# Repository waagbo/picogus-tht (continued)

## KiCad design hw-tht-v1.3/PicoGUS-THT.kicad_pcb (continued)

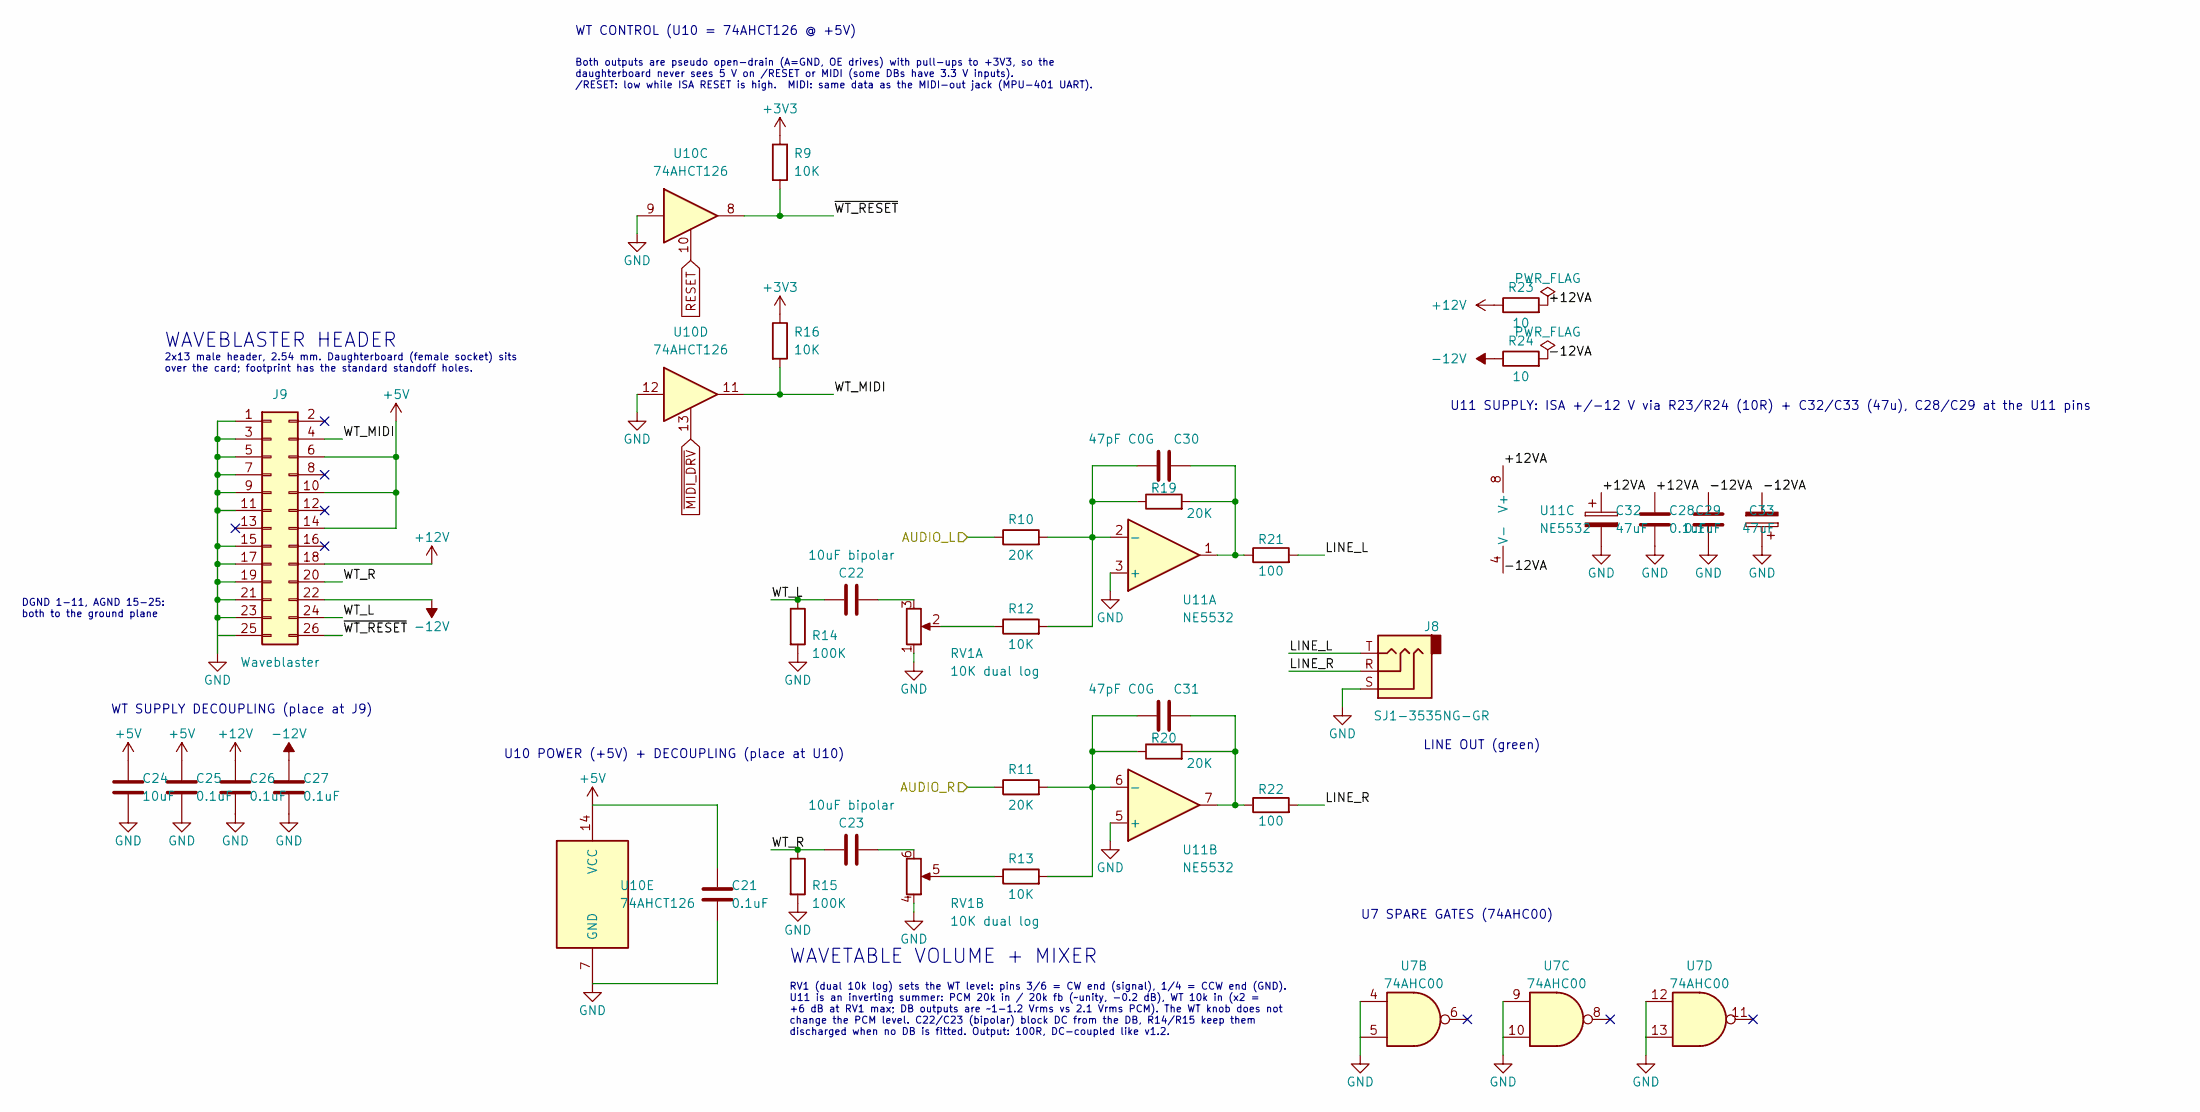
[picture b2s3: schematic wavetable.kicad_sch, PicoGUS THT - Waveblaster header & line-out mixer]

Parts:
C21, C25, C26, C27, C28, C29: 0.1uF; C_Disc_D5.0mm_W2.5mm_P5.00mm; MPN RDER71H104K0M1H03A; DigiKey 490-9144-1-ND
C22, C23: 10uF bipolar; C_Radial_D6.3mm_H11.0mm_P2.50mm; MPN ECE-A1HN100U; DigiKey P1280-ND
C24: 10uF; C_Disc_D5.0mm_W2.5mm_P5.00mm; MPN RCER71H106MWK1H03B; DigiKey 490-11888-ND
C30, C31: 47pF C0G; C_Disc_D5.0mm_W2.5mm_P5.00mm; MPN K470J15C0GF5TH5; DigiKey BC1038CT-ND
C32, C33: 47uF; CP_Radial_D5.0mm_P2.00mm; MPN 35YXJ47M5X11; DigiKey 1189-2919-ND
J8: SJ1-3535NG-GR; Jack_3.5mm_CUI_SJ1-3535NG_Horizontal; MPN SJ1-3535NG-GR; DigiKey CP1-3535NG-GR-ND
J9: Waveblaster; Wavetable_NoMountingHoles; MPN 77313-118-26LF; DigiKey 609-5706-ND
R9, R12, R13, R16: 10K; R_Axial_DIN0207_L6.3mm_D2.5mm_P10.16mm_Horizontal; MPN MFR-25FBF52-10K; DigiKey 10.0KXBK-ND
R10, R11, R19, R20: 20K; R_Axial_DIN0207_L6.3mm_D2.5mm_P10.16mm_Horizontal; MPN MFR-25FBF52-20K; DigiKey 20.0KXBK-ND
R14, R15: 100K; R_Axial_DIN0207_L6.3mm_D2.5mm_P10.16mm_Horizontal; MPN MFR-25FBF52-100K; DigiKey 100KXBK-ND
R21, R22: 100; R_Axial_DIN0207_L6.3mm_D2.5mm_P10.16mm_Horizontal; MPN MFR-25FBF52-100R; DigiKey 100XBK-ND
R23, R24: 10; R_Axial_DIN0207_L6.3mm_D2.5mm_P10.16mm_Horizontal; MPN MFR-25FBF52-10R; DigiKey 10.0XBK-ND
RV1: 10K dual log; Potentiometer_Alps_RK097_Dual_Horizontal_Switch; MPN PTD902-2015F-A103; DigiKey PTD902-2015F-A103-ND
U7: 74AHC00; DIP-14_W7.62mm; MPN SN74AHC00N; DigiKey 296-4510-5-ND
U10: 74AHCT126; DIP-14_W7.62mm; MPN SN74AHCT126N; DigiKey 296-4659-5-ND
U11: NE5532; DIP-8_W7.62mm; MPN NE5532P; DigiKey 296-1410-5-ND

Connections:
+3V3: R9.1, R16.1; also elsewhere on the board
+5V: C21.1, C24.1, C25.1, J9.6, J9.10, J9.14, U10.14 (VCC); also elsewhere on the board
+12V: C26.1, J9.18, R23.1; also elsewhere on the board
-12V: C27.1, J9.22, R24.1; also elsewhere on the board
/PCM5100 audio/AUDIO_L: R10.1; also elsewhere on the board
/PCM5100 audio/AUDIO_R: R11.1; also elsewhere on the board
/Wavetable & line out/+12VA: C28.1, C32.1, R23.2, U11.8 (V+)
/Wavetable & line out/-12VA: C29.2, C33.2, R24.2, U11.4 (V-)
/Wavetable & line out/LINE_L: J8.T, R21.2
/Wavetable & line out/LINE_R: J8.R, R22.2
/Wavetable & line out/WT_L: C22.1, J9.24, R14.1
/Wavetable & line out/WT_MIDI: J9.4, R16.2, U10.11
/Wavetable & line out/WT_R: C23.1, J9.20, R15.1
/Wavetable & line out/~WT_RESET: J9.26, R9.2, U10.8
GND: C21.2, C24.2, C25.2, C26.2, C27.2, C28.2, C29.1, C32.2, C33.1, J8.S, J9.1, J9.3, J9.5, J9.7, J9.9, J9.11, J9.15, J9.17, J9.19, J9.21, J9.23, J9.25, R14.2, R15.2, RV1.1, RV1.4, U7.4, U7.5, U7.9, U7.10, U7.12, U7.13, U10.7 (GND), U10.9, U10.12, U11.3 (+), U11.5 (+); also elsewhere on the board
unnamed: C22.2, RV1.3
unnamed: C23.2, RV1.6
unnamed: C30.2, R19.2, R21.1, U11.1
unnamed: C31.2, R20.2, R22.1, U11.7
unnamed: R12.1, RV1.2
unnamed: R13.1, RV1.5
unnamed: C30.1, R10.2, R12.2, R19.1, U11.2 (-)
unnamed: C31.1, R11.2, R13.2, R20.1, U11.6 (-)
RESET: U10.10; also elsewhere on the board
~MIDI_DRV: U10.13; also elsewhere on the board

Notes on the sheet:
DGND 1-11, AGND 15-25: both to the ground plane
WAVEBLASTER HEADER
2x13 male header, 2.54 mm. Daughterboard (female socket) sits over the card; footprint has the standard standoff holes.
WT SUPPLY DECOUPLING (place at J9)
U10 POWER (+5V) + DECOUPLING (place at U10)
WT CONTROL (U10 = 74AHCT126 @ +5V)
Both outputs are pseudo open-drain (A=GND, OE drives) with pull-ups to +3V3, so the daughterboard never sees 5 V on /RESET or MIDI (some DBs have 3.3 V inputs). /RESET: low while ISA RESET is high. MIDI: same data as the MIDI-out jack (MPU-401 UART).
U11 SUPPLY: ISA +/-12 V via R23/R24 (10R) + C32/C33 (47u), C28/C29 at the U11 pins
WAVETABLE VOLUME + MIXER
RV1 (dual 10k log) sets the WT level: pins 3/6 = CW end (signal), 1/4 = CCW end (GND). U11 is an inverting summer: PCM 20k in / 20k fb (~unity, -0.2 dB), WT 10k in (x2 = +6 dB at RV1 max; DB outputs are ~1-1.2 Vrms vs 2.1 Vrms PCM). The WT knob does not change the PCM level. C22/C23 (bipolar) block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
LINE OUT (green)
U7 SPARE GATES (74AHC00)

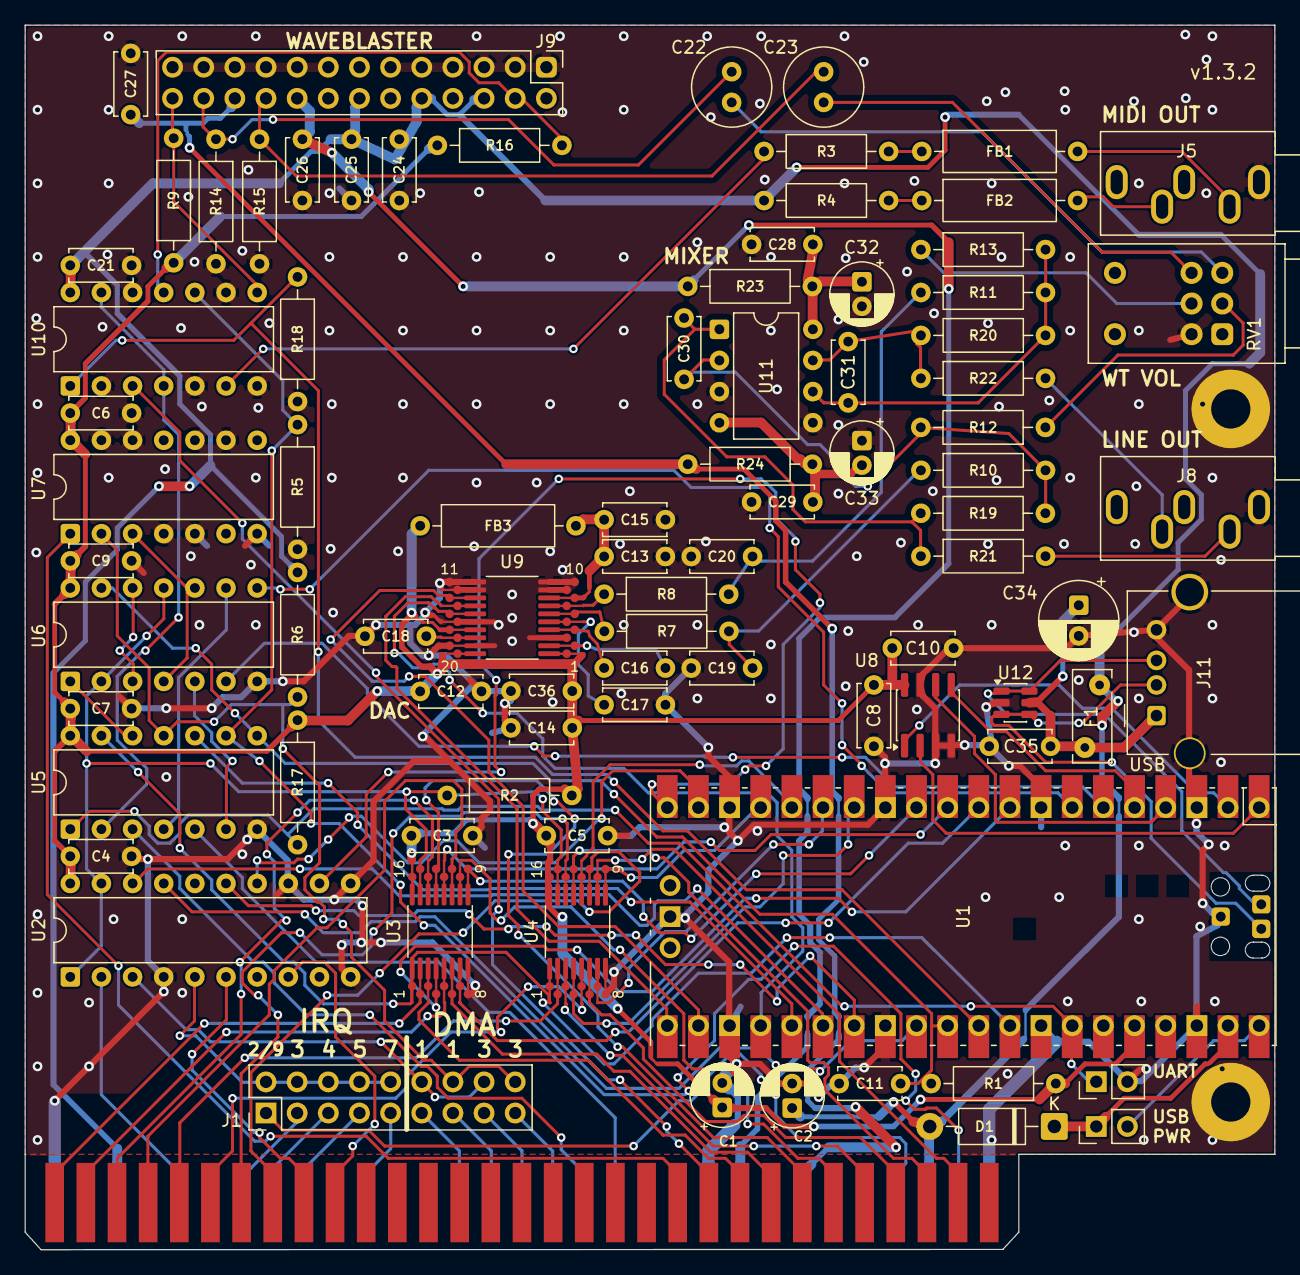
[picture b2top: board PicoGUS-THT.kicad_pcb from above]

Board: 2 copper layers, 101.9 x 99.8 mm, 88 parts (0 on the bottom side), 110 nets.

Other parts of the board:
C34: 220uF; CP_Radial_D6.3mm_P2.50mm
C35: 0.1uF; C_Disc_D5.0mm_W2.5mm_P5.00mm
F1: 0.5A PTC; Fuse_Bourns_MF-RHT050
J11: USB-A; USB_A_Molex_67643_Horizontal
U12: USBLC6-2SC6; SOT-23-6

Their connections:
+5V: F1.1; also elsewhere on the board
/USB host port/VBUS_USB: C34.1, C35.1, F1.2, J11.1, U12.5
GND: C34.2, C35.2, J11.4, J11.SH, U12.2; also elsewhere on the board
USB_DM: J11.2, U12.3, U12.4; also elsewhere on the board
USB_DP: J11.3, U12.1, U12.6; also elsewhere on the board

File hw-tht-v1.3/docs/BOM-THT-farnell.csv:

Quantity,Manufacturer Part Number,Manufacturer,Customer Part Number,Description
1,SC0915,Raspberry Pi,PicoGUS-THT-1.3.2: U1,Raspberry Pi Pico
1,SN74AHC244N,Texas Instruments,PicoGUS-THT-1.3.2: U2,74AHC244
2,SN74CB3T3257PWR,Texas Instruments,"PicoGUS-THT-1.3.2: U3,U4",SN74CB3T3257
1,SN74AHC14N,Texas Instruments,PicoGUS-THT-1.3.2: U5,74AHC14
2,SN74AHC00N,Texas Instruments,"PicoGUS-THT-1.3.2: U6,U7",74AHC00
1,APS6404L-3SQR-SN,AP Memory,PicoGUS-THT-1.3.2: U8,APS6404L-3SQR-SN
1,PCM5100APWR,Texas Instruments,PicoGUS-THT-1.3.2: U9,PCM5100A
1,SN74AHCT126N,Texas Instruments,PicoGUS-THT-1.3.2: U10,74AHCT126
1,1N5819RLG,onsemi,PicoGUS-THT-1.3.2: D1,1N5819
2,RNMF14FTC220R,Stackpole,"PicoGUS-THT-1.3.2: R3,R4",220R
2,RNMF14FTC470R,Stackpole,"PicoGUS-THT-1.3.2: R7,R8",470R
1,MFR-25FBF52-1K,Yageo,PicoGUS-THT-1.3.2: R1,1k
5,MFR-25FBF52-10K,Yageo,"PicoGUS-THT-1.3.2: R9,R12,R13,R16,R17",10k
4,MFR-25FBF52-20K,Yageo,"PicoGUS-THT-1.3.2: R10,R11,R19,R20",20k
3,MFR-25FBF52-15K,Yageo,"PicoGUS-THT-1.3.2: R2,R5,R6",15k
20,RDER71H104K0M1H03A,Murata,"PicoGUS-THT-1.3.2: C3-9,11-14,18,21,25-29,35,36",0.1uF
1,RDER71H105K2M1H03A,Murata,PicoGUS-THT-1.3.2: C10,1uF
2,FG24X7R1H225KRT06,TDK,"PicoGUS-THT-1.3.2: C16,C17",2.2uF
2,RCER71H106MWK1H03B,Murata,"PicoGUS-THT-1.3.2: C15,C24",10uF
2,FG28C0G1H222JNT06,TDK,"PicoGUS-THT-1.3.2: C19,C20",2.2nF C0G
4,35YXJ47M5X11,Rubycon,"PicoGUS-THT-1.3.2: C1,C2,C32,C33",47uF
2,ECE-A1HN100U,Panasonic,"PicoGUS-THT-1.3.2: C22,C23",10uF bipolar
3,2743002112,Fair-Rite,"PicoGUS-THT-1.3.2: FB1,FB2,FB3",Ferrite bead
1,PTD902-2015F-A103,Bourns,PicoGUS-THT-1.3.2: RV1,10k dual log
1,77313-118-18LF,Amphenol ICC (FCI),PicoGUS-THT-1.3.2: J1,"2x9 header, gold"
4,M7582-05,Harwin,"PicoGUS-THT-1.3.2: J1,J7 shunts",2.54mm jumper shunt
2,77311-118-02LF,Amphenol ICC (FCI),"PicoGUS-THT-1.3.2: J6,J7","1x2 header, gold"
1,SJ1-3535NG,Same Sky (CUI),PicoGUS-THT-1.3.2: J5,SJ1-3535NG (black)
1,SJ1-3535NG-GR,Same Sky (CUI),PicoGUS-THT-1.3.2: J8,SJ1-3535NG-GR (green)
1,77313-118-26LF,Amphenol ICC (FCI),PicoGUS-THT-1.3.2: J9,"Waveblaster 2x13 male, gold"
1,0676430910,Molex,PicoGUS-THT-1.3.2: J11,USB-A receptacle
1,MF-R050,Bourns,PicoGUS-THT-1.3.2: F1,0.5A PTC
1,16ZLH220MEFC6.3X11,Rubycon,PicoGUS-THT-1.3.2: C34,220uF
1,USBLC6-2SC6,STMicroelectronics,PicoGUS-THT-1.3.2: U12 (optional),USBLC6-2SC6
1,NE5532P,Texas Instruments,PicoGUS-THT-1.3.2: U11,NE5532
3,MFR-25FBF52-100K,Yageo,"PicoGUS-THT-1.3.2: R14,R15,R18",100k
2,MFR-25FBF52-10R,Yageo,"PicoGUS-THT-1.3.2: R23,R24",10R
2,MFR-25FBF52-100R,Yageo,"PicoGUS-THT-1.3.2: R21,R22",100R
2,K470J15C0GF5TH5,Vishay,"PicoGUS-THT-1.3.2: C30,C31",47pF C0G

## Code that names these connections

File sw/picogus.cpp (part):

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#ifdef ASYNC_UART
#include "stdio_async_uart.h"
#endif 
// UART_TX_PIN is defined in isa_io.pio.h
#define UART_RX_PIN (-1)
#define UART_ID     uart0
#define BAUD_RATE   230400
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
#ifdef PICOGUS_BOOTROM_SEL0_PIN
// Experimental boot ROM of the PicoGUS v2.1 THT: U17 (74HCT153) passes one of the decoder's outputs to the flash's
// chip enable, as ROM_SEL1 (GPIO3) and ROM_SEL0 (GPIO2) select, or +5 V (off) when both are high, as R35/R36 hold
// them until the firmware drives them.
static void bootrom_apply(uint8_t base) {
    //                              off  C800 D000 D800
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    busy_wait_ms(250);
    overclock_370mhz();
#ifdef ASYNC_UART
    stdio_async_uart_init_full(UART_ID, BAUD_RATE, UART_TX_PIN, UART_RX_PIN);
#else
    stdio_init_all();
#endif
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    if (*reset_reason & PLATFORM_CHIP_RESET_HAD_POWER_ON_BITS) {
        DBG_PUTS("I was reset due to power on reset or brownout detection.");
    } else if (*reset_reason & PLATFORM_CHIP_RESET_HAD_RUN_PIN_BITS) {
        DBG_PUTS("I was reset due to the RUN pin (either manually or due to ISA RESET signal)");
    } else if(*reset_reason & PLATFORM_CHIP_RESET_HAD_DEBUG_BITS) {
        DBG_PUTS("I was reset due the debug port");
    }
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    gpio_set_dir_out_masked((1u << PICOGUS_BOOTROM_SEL0_PIN) | (1u << PICOGUS_BOOTROM_SEL1_PIN));
#endif
#else
    // Determine board type. GPIO 29 is grounded on PicoGUS v2.0, and on a Pico, it's VSYS/3 (~1.666V)
    // GPIO 25 must be high to read GPIO 29 on the Pico W
    gpio_init(25);
    gpio_set_dir(25, GPIO_OUT);
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    if (BOARD_TYPE == PICO_BASED) {
        // Original hardware drives MIDI directly from RP2040. Newer HW uses an open drain inverter
        // PicoGUS v1.2 also uses an open drain but we can't detect that particular board
        gpio_set_drive_strength(UART_TX_PIN, GPIO_DRIVE_STRENGTH_12MA);
    }
    gpio_set_function(UART_TX_PIN, GPIO_FUNC_UART);
#endif // SOUND_MPU

#ifdef PSRAM_CORE0
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        platform_gpio_enable_input(i);
        gpio_disable_pulls(i);
    }
    platform_gpio_enable_input(IOW_PIN);
    platform_gpio_enable_input(IOR_PIN);
    platform_gpio_enable_input(DACK_PIN);
    gpio_disable_pulls(IOW_PIN);
    gpio_disable_pulls(IOR_PIN);
    gpio_pull_down(IOCHRDY_PIN);
    gpio_set_dir(IOCHRDY_PIN, GPIO_OUT);

    DBG_PUTS("Enabling bus transceivers...");
    // waggle ADS to set BUSOE latch
    gpio_init(ADS_PIN);
    gpio_set_dir(ADS_PIN, GPIO_OUT);
    gpio_put(ADS_PIN, 1);
    busy_wait_ms(10);
    gpio_put(ADS_PIN, 0);

    DBG_PUTS("Starting ISA bus PIO...");
    // gpio_set_drive_strength(ADS_PIN, GPIO_DRIVE_STRENGTH_12MA);
    gpio_set_slew_rate(ADS_PIN, GPIO_SLEW_RATE_FAST);

    uint iow_offset = pio_add_program(pio0, &iow_program);
    pio_sm_claim(pio0, IOW_PIO_SM);
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
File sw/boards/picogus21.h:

// Board config file for PicoGUS v2.1 THT: the PicoGUS 2.0 circuit on a
// Waveshare Core2350B2 module (RP2350B, 16 MB flash, 8 MB PSRAM on QMI CS1).
// Same GPIO map as PicoGUS 2.0; the GUS sample RAM is the module's PSRAM
// (PSRAM_QMI) instead of v2.0's APS6404L on GPIO0-3.

// The below lines aren't just comments - they're directives to the Pico SDK cmake system
// pico_cmake_set PICO_PLATFORM = rp2350
// pico_cmake_set PICO_CYW43_SUPPORTED = 1
// pico_cmake_set_default PICO_FLASH_SIZE_BYTES = (16 * 1024 * 1024)
// pico_cmake_set PICO_RP2350_A2_SUPPORTED = 0
// (no RP2350-E10 workaround block in UF2s, see pico2_fast.h)

#ifndef _BOARDS_PICOGUS21_H
#define _BOARDS_PICOGUS21_H

// For board detection: the firmware can't tell this board apart at runtime
// (v2.0 is recognised by GPIO29 on the ADC, and the RP2350B ADC is GPIO40-47)
#define PICOGUS_BOARD_V21 1

// RP2350B: 48 GPIOs
#define PICO_RP2350A 0

// Waveshare Core2350B: 12 MHz crystal, 16 MB W25Q128-class flash
#define PICO_XOSC_STARTUP_DELAY_MULTIPLIER 64
#ifndef PICO_FLASH_SIZE_BYTES
#define PICO_FLASH_SIZE_BYTES (16 * 1024 * 1024)
#endif

// PSRAM on the module: chip select is QMI CS1 on GPIO47 (Core2350B1/B2)
#define PICOGUS_PSRAM_QMI_CS_PIN 47

// The carrier's activity LED is GPIO23, as on PicoGUS 2.0. The module's own
// LED is on GPIO39.
#ifndef PICO_DEFAULT_LED_PIN
#define PICO_DEFAULT_LED_PIN 23
#endif

// --- UART: MIDI/debug out on GPIO28, as on every PicoGUS ---
#ifndef PICO_DEFAULT_UART
#define PICO_DEFAULT_UART 0
#endif
#ifndef PICO_DEFAULT_UART_TX_PIN
#define PICO_DEFAULT_UART_TX_PIN 28
#endif

// --- Radio Module 2 (U14, CYW43439), optional: wired as on the Pico W, on four
// of the module's free GPIOs. Data and clock share one PIO, so both are in the
// GPIO16-47 window. BT_ON is tied to WL_ON on the card; the RM2's own GPIO0-2
// (on a Pico W: LED, SMPS mode, VBUS sense) are not connected.
#ifndef CYW43_WL_GPIO_COUNT
#define CYW43_WL_GPIO_COUNT 3
#endif
#ifndef CYW43_WL_GPIO_LED_PIN
#define CYW43_WL_GPIO_LED_PIN 0
#endif
#ifndef CYW43_PIN_WL_DYNAMIC
#define CYW43_PIN_WL_DYNAMIC 0
#endif
#ifndef CYW43_DEFAULT_PIN_WL_REG_ON
#define CYW43_DEFAULT_PIN_WL_REG_ON 40u
#endif
#ifndef CYW43_DEFAULT_PIN_WL_DATA_OUT
#define CYW43_DEFAULT_PIN_WL_DATA_OUT 44u
#endif
#ifndef CYW43_DEFAULT_PIN_WL_DATA_IN
#define CYW43_DEFAULT_PIN_WL_DATA_IN 44u
#endif
#ifndef CYW43_DEFAULT_PIN_WL_HOST_WAKE
#define CYW43_DEFAULT_PIN_WL_HOST_WAKE 44u
#endif
#ifndef CYW43_DEFAULT_PIN_WL_CLOCK
#define CYW43_DEFAULT_PIN_WL_CLOCK 45u
#endif
#ifndef CYW43_DEFAULT_PIN_WL_CS
#define CYW43_DEFAULT_PIN_WL_CS 42u
#endif

// --- Boot ROM (experimental; U15 flash in a PLCC-32 socket, U16 74HCT138 decoder, U17 74HCT153):
// ROM_SEL1 (GPIO3) and ROM_SEL0 (GPIO2) pick the base address: high high = off, high low = D0000h,
// low high = C8000h, low low = D8000h. 10k pull-ups (R35, R36) keep the ROM off until the firmware
// drives the pins. The base is a saved setting (pgusinit /bootrom, off by default; the firmware
// built with -DBOOTROM_ENABLE=ON defaults to D0000h).
#define PICOGUS_BOOTROM_SEL0_PIN 2
#define PICOGUS_BOOTROM_SEL1_PIN 3

// --- FLASH: W25Q128-class, set up by the embedded XIP setup function ---
#define PICO_BOOT_STAGE2_CHOOSE_W25Q080 1

// Slower flash for running at 370MHz, see pico2_fast.h
#define PICO_FLASH_SPI_CLKDIV 6
#define PICO_FLASH_SPI_RXDELAY 4

#endif

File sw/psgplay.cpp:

/*
 *  Copyright (C) 2022-2024  Ian Scott
 *
 *  This program is free software; you can redistribute it and/or modify
 *  it under the terms of the GNU General Public License as published by
 *  the Free Software Foundation; either version 2 of the License, or
 *  (at your option) any later version.
 *
 *  This program is distributed in the hope that it will be useful,
 *  but WITHOUT ANY WARRANTY; without even the implied warranty of
 *  MERCHANTABILITY or FITNESS FOR A PARTICULAR PURPOSE.  See the
 *  GNU General Public License for more details.
 *
 *  You should have received a copy of the GNU General Public License along
 *  with this program; if not, write to the Free Software Foundation, Inc.,
 *  51 Franklin Street, Fifth Floor, Boston, MA 02110-1301, USA.
 */

#include "include/pg_debug.h"

#if PICO_ON_DEVICE
#include "hardware/clocks.h"
#include "hardware/structs/clocks.h"
#include "hardware/pwm.h"
#include "hardware/pio.h"
#endif

#include "pico/stdlib.h"
#include "audio/audio_i2s_minimal.h"
#include "audio/volctrl.h"
#include "audio/clamp.h"

#include "square/square.h"

#include "include/cmd_buffers.h"

#if SOUND_TANDY
extern tandy_buffer_t tandy_buffer;
#endif
#if SOUND_CMS
extern cms_buffer_t cms_buffer;
#endif

extern uint LED_PIN;

#ifdef USB_STACK
#include "tusb.h"
#endif
#ifdef PGDFS
#include "dfs/dfs.h"
#endif
#ifdef USB_MSC
#include "usb_msc/msc_app.h"
#endif // USB_MSC
#if defined(USB_MOUSE) || defined(SOUND_MPU)
#include "system/pico_pic.h"
#endif

#ifdef USB_MOUSE
#include "mouse/8250uart.h"
#include "mouse/sermouse.h"
#endif

#if PICO_ON_DEVICE
#include "pico/binary_info.h"
bi_decl(bi_3pins_with_names(PICO_AUDIO_I2S_DATA_PIN, "I2S DIN", PICO_AUDIO_I2S_CLOCK_PIN_BASE, "I2S BCK", PICO_AUDIO_I2S_CLOCK_PIN_BASE+1, "I2S LRCK"));
#endif

#ifdef SOUND_MPU
#include "system/flash_settings.h"
extern Settings settings;
#include "mpu401/export.h"
#endif

#ifdef WEBSERVER
#include "web/web.h"
#endif
#ifdef CAPTURE
#include "capture/capture.h"
#endif

#define audio_pio __CONCAT(pio, PICO_AUDIO_I2S_PIO)

static void init_audio(void) {
    const audio_i2s_config_t config = {
            .data_pin = PICO_AUDIO_I2S_DATA_PIN,
            .clock_pin_base = PICO_AUDIO_I2S_CLOCK_PIN_BASE,
            .dma_channel = 6,
            .pio_sm = PICO_AUDIO_I2S_SM,
    };
    audio_i2s_minimal_setup(&config, 44100);
}

#if SOUND_TANDY
static tandysound_t tandysound;
#endif
#if SOUND_CMS
static cms_t cms;
#endif

// Setup values for audio sample clock
static constexpr uint32_t clocks_per_sample_minus_one = (RP2_CLOCK_SPEED * 1000u / 44100) - 1;
static constexpr uint pwm_slice_num = 4; // slices 0-3 are taken by USB joystick support

// PSG generation is cheap (phase accumulators + volume lookups per voice), so
// synthesize directly in the ISR — no intermediate FIFO needed.
void audio_sample_handler(void) {
    pwm_clear_irq(pwm_slice_num);

    int32_t buf[2] = {0, 0};
#if SOUND_TANDY
    tandysound.generator().generate_frames(buf, 1);
#endif
#if SOUND_CMS
    cms.generator(0).generate_frames(buf, 1);
    cms.generator(1).generate_frames(buf, 1);
#endif
    int32_t sample_l = scale_sample(clamp16(buf[0]), volume.psg, 0);
    int32_t sample_r = scale_sample(clamp16(buf[1]), volume.psg, 0);
    sample_l = clamp16(sample_l);
    sample_r = clamp16(sample_r);

    audio_pio->txf[PICO_AUDIO_I2S_SM] = ((sample_l & 0xFFFF) | (sample_r << 16));
}

void play_psg() {
    DBG_PUTS("starting core 1 psg");
    // flash_safe_execute_core_init();

#if defined(USB_MOUSE) || defined(SOUND_MPU)
    // Init PIC on this core so it handles timers
    PIC_Init();
    DBG_PUTS("pic inited on core 1");
#endif
#ifdef USB_STACK
    // Init TinyUSB for joystick support
    tuh_init(BOARD_TUH_RHPORT);
    // Pump USB events for ~500 ms so any device already connected at boot
    // is fully enumerated before the audio loop starts.
    {
        uint32_t deadline = time_us_32() + 500000u;
        while (time_us_32() < deadline) tuh_task();
    }
#endif

#ifdef SOUND_MPU
    MPU401_Init(settings.MPU.delaySysex, settings.MPU.fakeAllNotesOff, settings.MPU.waitBusyStatus);
#endif

    init_audio();
    set_volume(CMD_PSGVOL);

    // Use the PWM peripheral to trigger an IRQ at 44100Hz
    pwm_config pwm_c = pwm_get_default_config();
    pwm_config_set_wrap(&pwm_c, clocks_per_sample_minus_one);
    pwm_init(pwm_slice_num, &pwm_c, false);
    pwm_set_irq_enabled(pwm_slice_num, true);
    irq_set_exclusive_handler(PWM_IRQ_WRAP, audio_sample_handler);
    irq_set_priority(PWM_IRQ_WRAP, PICO_LOWEST_IRQ_PRIORITY);
    irq_set_enabled(PWM_IRQ_WRAP, true);
    pwm_set_enabled(pwm_slice_num, true);

    for (;;) {
        bool notfirst = false;
#if SOUND_TANDY
        while (tandy_buffer.tail != tandy_buffer.head) {
            if (!notfirst) {
                gpio_xor_mask(LED_PIN);
                notfirst = true;
            }
            tandysound.write_register(0, tandy_buffer.cmds[tandy_buffer.tail]);
            ++tandy_buffer.tail;
        }
#endif // SOUND_TANDY
#if SOUND_CMS
        while (cms_buffer.tail != cms_buffer.head) {
            if (!notfirst) {
                gpio_xor_mask(LED_PIN);
                notfirst = true;
            }
            auto cmd = cms_buffer.cmds[cms_buffer.tail];
            if (cmd.addr & 1) {
                cms.write_addr(cmd.addr, cmd.data);
            } else {
                cms.write_data(cmd.addr, cmd.data);
            }
            ++cms_buffer.tail;
        }
#endif

#ifdef USB_STACK
        // Service TinyUSB events
        tuh_task();
#endif
#ifdef USB_MSC
        msc_app_task();   // mount/unmount the USB drive outside of FatFs calls
#endif // USB_MSC
#ifdef PGDFS
        dfs_tasks();
#endif
#ifdef CAPTURE
        capture_task();   // song recorder: events of the taps to files on the USB drive
#endif
#ifdef USB_MOUSE
        // mouse task
        sermouse_core1_task();

        // uart emulation task
        uartemu_core1_task();
#endif
#ifdef SOUND_MPU
        send_midi_bytes(8);
#endif
#ifdef WEBSERVER
        // Lowest priority work: PSG audio is synthesized in an interrupt
        web_task();
#endif
    }
}
